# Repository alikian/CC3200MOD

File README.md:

CC3200MOD Eagle Library and Breakout
=======================

Eagle Library for TI CC3200MOD and CC3200MOD Breakout board

For more info about Breakout please check the WiKi page https://github.com/alikian/CC3200MOD/wiki

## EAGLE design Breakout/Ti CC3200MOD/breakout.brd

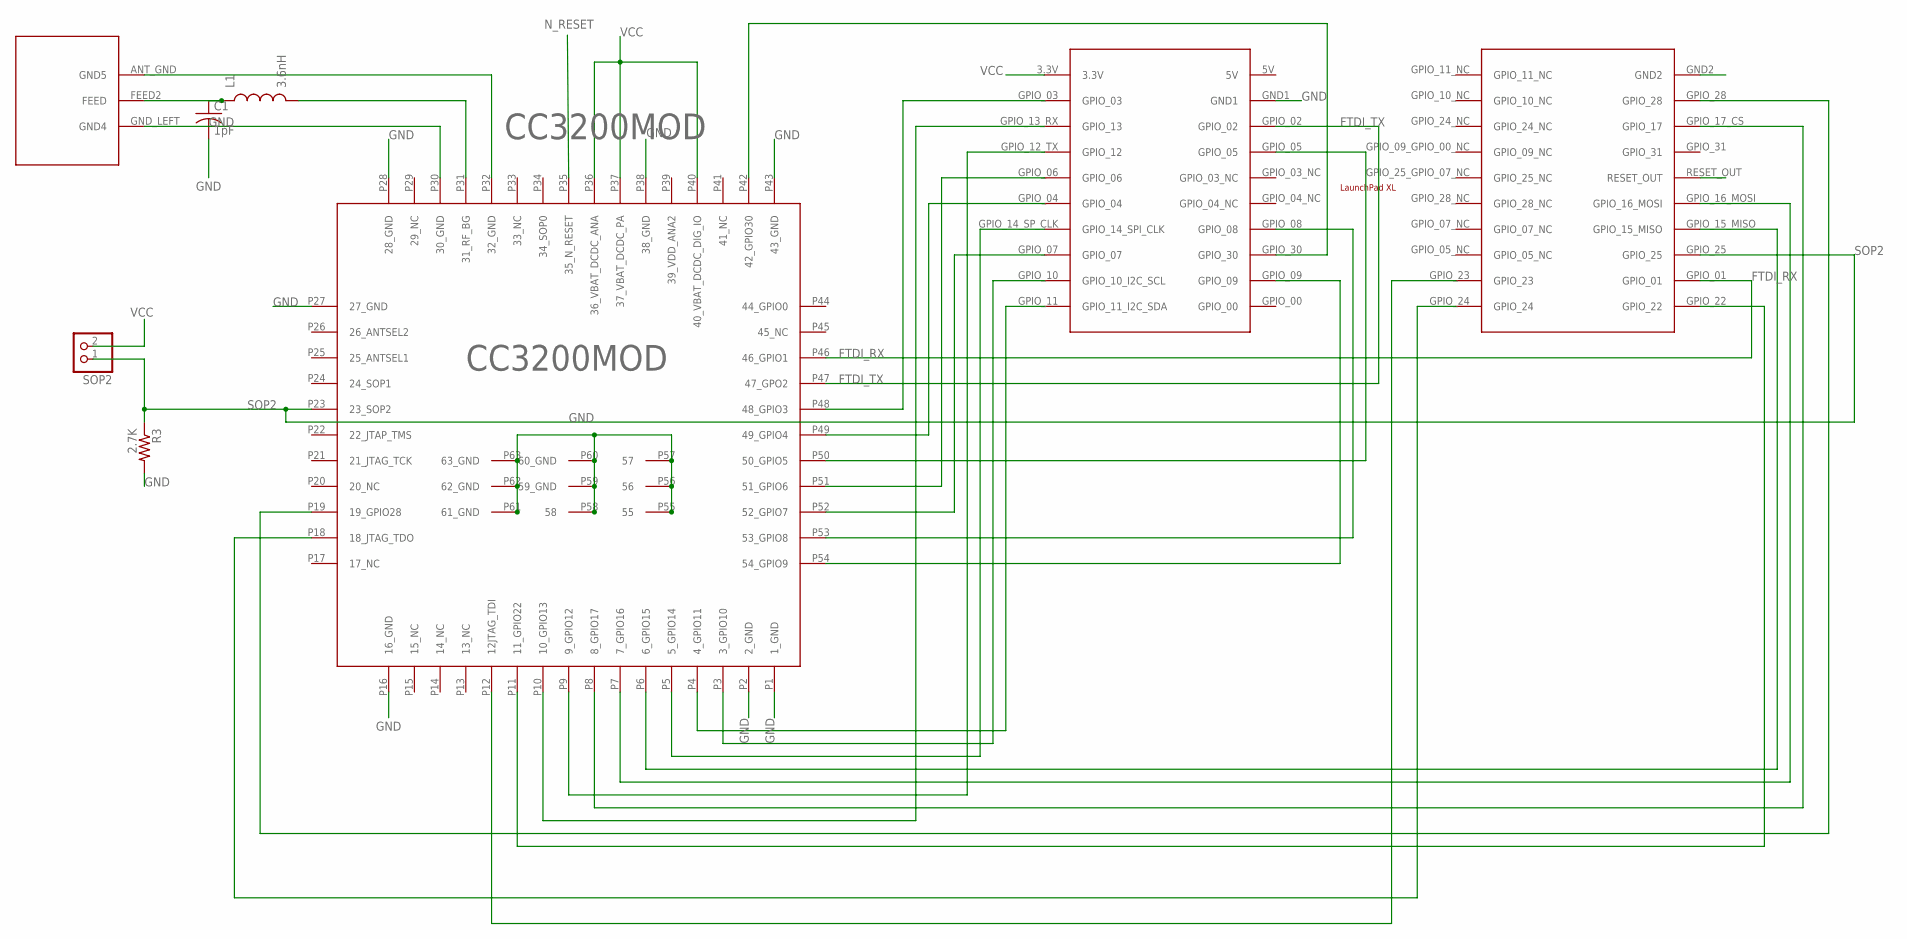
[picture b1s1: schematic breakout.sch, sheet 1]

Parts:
ANT_PAD: ANT
C1: 1pF; C0402
CC3200MOD: CC3200; CC3200MOD
L1: 3.6nH; C0402
R3: 2.7K; 0603-RES
SOP2: PINHD-1X2; 1X02
U11: XL; LAUNCHPADXL

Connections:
FTDI_RX: CC3200MOD.P46 (46_GPIO1), U11.GPIO_01; also elsewhere on the board
FTDI_TX: CC3200MOD.P47 (47_GPO2), U11.GPIO_02; also elsewhere on the board
GND: ANT_PAD.ANT_GND (GND5), ANT_PAD.GND_LEFT (GND4), C1.2, CC3200MOD.P1 (1_GND), CC3200MOD.P2 (2_GND), CC3200MOD.P16 (16_GND), CC3200MOD.P27 (27_GND), CC3200MOD.P28 (28_GND), CC3200MOD.P30 (30_GND), CC3200MOD.P32 (32_GND), CC3200MOD.P38 (38_GND), CC3200MOD.P43 (43_GND), CC3200MOD.P55 (55), CC3200MOD.P56 (56), CC3200MOD.P57 (57), CC3200MOD.P58 (58), CC3200MOD.P59 (59_GND), CC3200MOD.P60 (60_GND), CC3200MOD.P61 (61_GND), CC3200MOD.P62 (62_GND), CC3200MOD.P63 (63_GND), R3.2, U11.GND1, U11.GND2; also elsewhere on the board
GPIO_05: CC3200MOD.P50 (50_GPIO5), U11.GPIO_05; also elsewhere on the board
GPIO_10: CC3200MOD.P3 (3_GPIO10), U11.GPIO_10 (GPIO_10_I2C_SCL); also elsewhere on the board
GPIO_11: CC3200MOD.P4 (4_GPIO11), U11.GPIO_11 (GPIO_11_I2C_SDA); also elsewhere on the board
GPIO_13: CC3200MOD.P10 (10_GPIO13), U11.GPIO_13_RX (GPIO_13); also elsewhere on the board
GPIO_22: CC3200MOD.P11 (11_GPIO22), U11.GPIO_22
GPIO_30: CC3200MOD.P42 (42_GPIO30), U11.GPIO_30; also elsewhere on the board
JTAG_TDI: CC3200MOD.P12 (12JTAG_TDI), U11.GPIO_23
JTAG_TDO: CC3200MOD.P18 (18_JTAG_TDO), U11.GPIO_24
unnamed: ANT_PAD.FEED2 (FEED), C1.1, L1.1
unnamed: CC3200MOD.P31 (31_RF_BG), L1.2
unnamed: CC3200MOD.P6 (6_GPIO15), U11.GPIO_15_MISO
unnamed: CC3200MOD.P7 (7_GPIO16), U11.GPIO_16_MOSI
unnamed: CC3200MOD.P8 (8_GPIO17), U11.GPIO_17_CS (GPIO_17)
unnamed: CC3200MOD.P5 (5_GPIO14), U11.GPIO_14_SP_CLK (GPIO_14_SPI_CLK)
unnamed: CC3200MOD.P19 (19_GPIO28), U11.GPIO_28
unnamed: CC3200MOD.P51 (51_GPIO6), U11.GPIO_06
unnamed: CC3200MOD.P49 (49_GPIO4), U11.GPIO_04
unnamed: CC3200MOD.P52 (52_GPIO7), U11.GPIO_07
unnamed: CC3200MOD.P53 (53_GPIO8), U11.GPIO_08
unnamed: CC3200MOD.P54 (54_GPIO9), U11.GPIO_09
unnamed: CC3200MOD.P9 (9_GPIO12), U11.GPIO_12_TX (GPIO_12)
unnamed: CC3200MOD.P48 (48_GPIO3), U11.GPIO_03
N_RESET: CC3200MOD.P35 (35_N_RESET), U11.RESET_OUT; also elsewhere on the board
SOP2: CC3200MOD.P23 (23_SOP2), R3.1, SOP2.1, U11.GPIO_25; also elsewhere on the board
VCC: CC3200MOD.P36 (36_VBAT_DCDC_ANA), CC3200MOD.P37 (37_VBAT_DCDC_PA), CC3200MOD.P40 (40_VBAT_DCDC_DIG_IO), SOP2.2, U11.3.3V; also elsewhere on the board

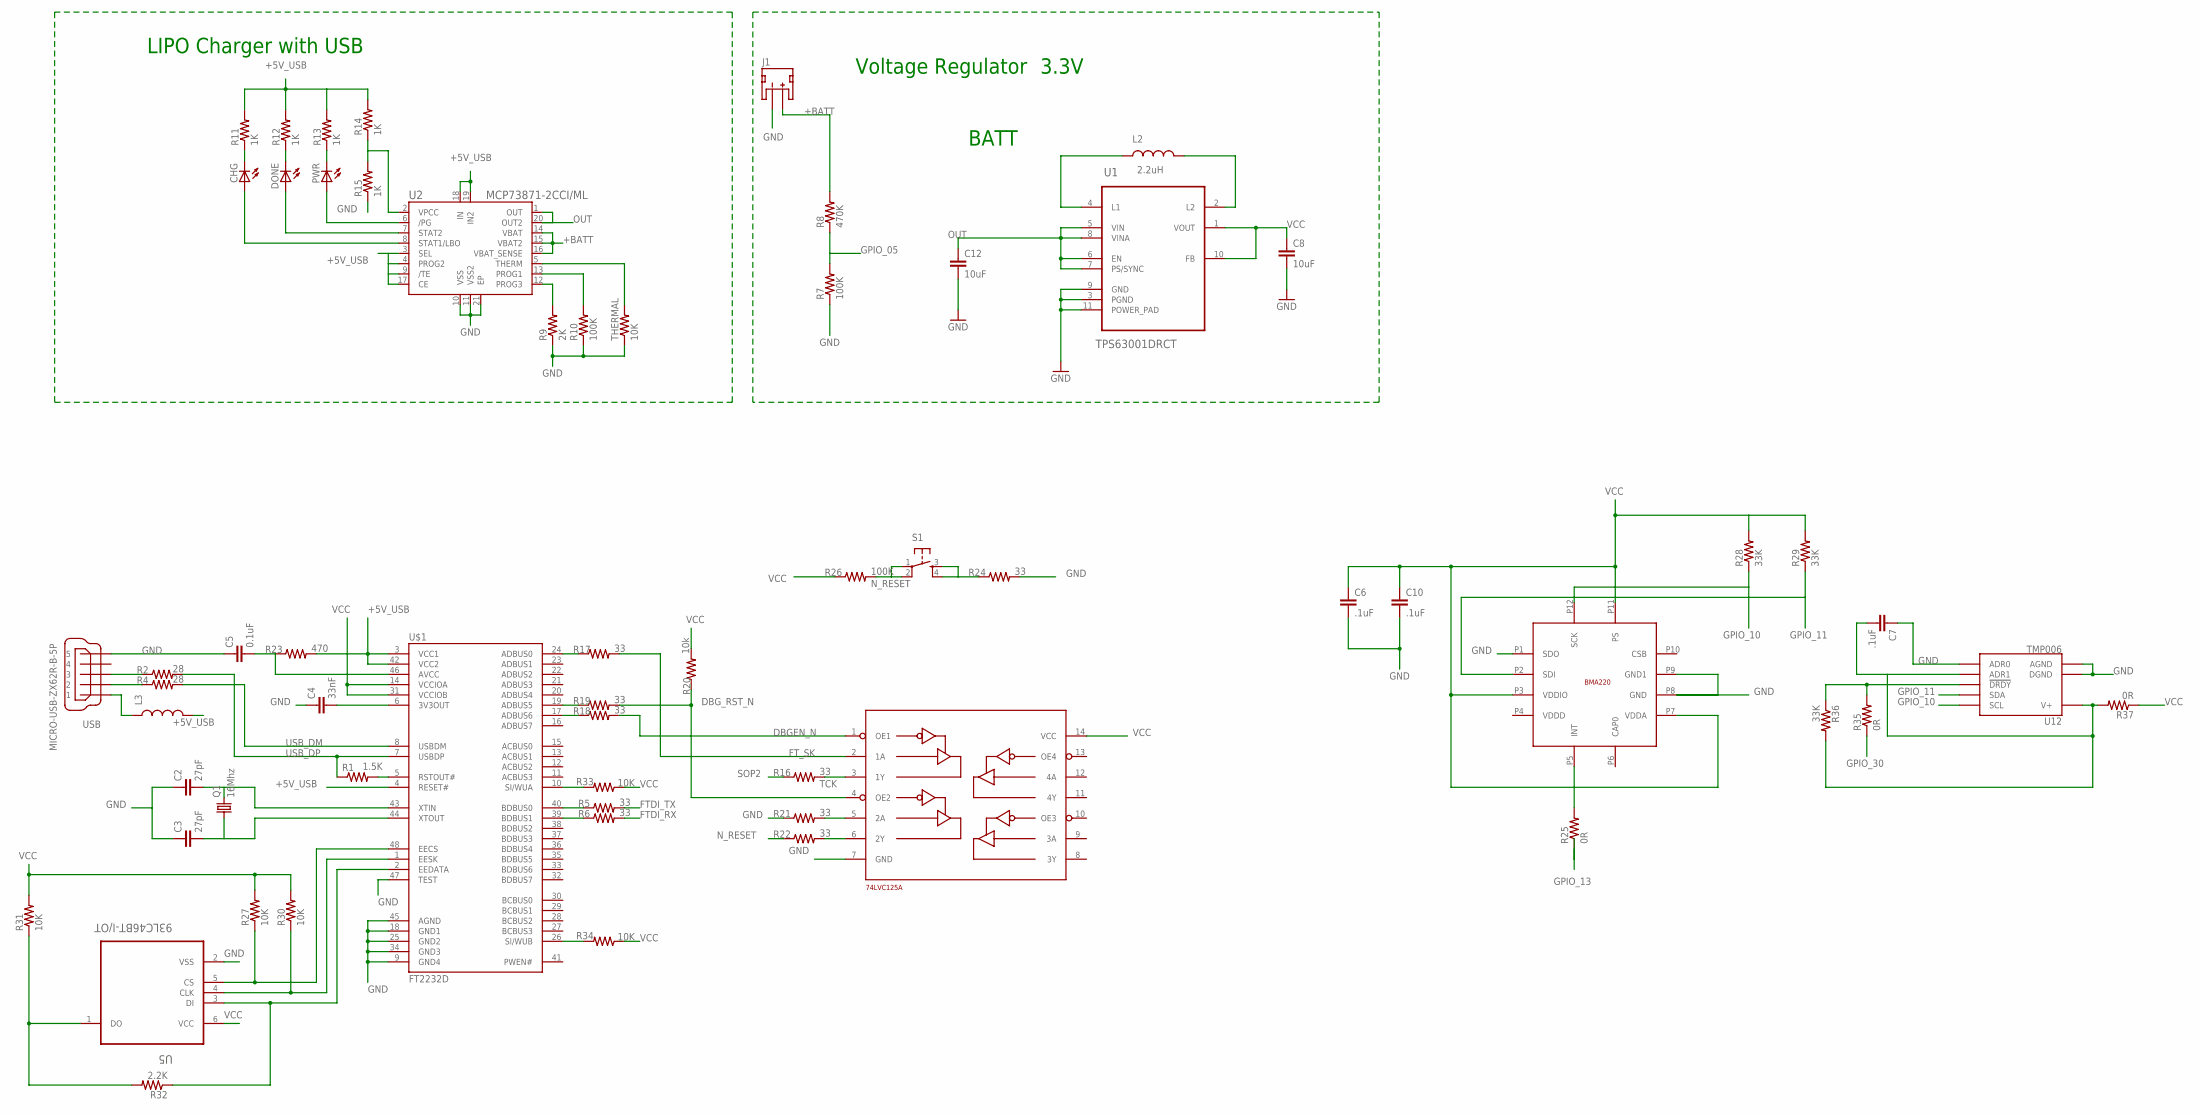
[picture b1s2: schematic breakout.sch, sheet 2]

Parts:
C2, C3: 27pF; 0402-CAP
C4: 33nF; 0402-CAP
C5: 0.1uF; 0402-CAP
C6, C7, C10: .1uF; 0402-CAP
C8, C12: 10uF; C0603
CHG: LEDSML0603; SML0603
DONE: LEDSML0603; SML0603
J1: JST_2MM_MALE; JST-2-SMD
L2: 2.2uH; 0805
L3: INDUCTOR-SPARKFUN0603; 0603
PWR: LEDSML0603; SML0603
Q1: 16Mhz; TC26H
R1: 1.5K; 0603-RES
R2, R4: 28; 0603-RES
R5, R6, R16, R17, R18, R19, R21, R22, R24: 33; 0603-RES
R7, R10, R26: 100K; 0603-RES
R8: 470K; 0603-RES
R9: 2K; 0603-RES
R11, R12, R13, R14, R15: 1K; 0603-RES
R20: 10k; 0603-RES
R23: 470; 0603-RES
R25, R35, R37: 0R; 0603-RES
R27, R30, R31, R33, R34: 10K; 0402-RES
R28, R29, R36: 33K; 0402-RES
R32: 2.2K; 0402-RES
S1: TAC_SWITCHSMD; TACTILE_SWITCH_SMD
THERMAL: 10K; 0603-RES
U1: TPS63001DRCT; SON50P300X300X100-11N
U2: MCP73871-2CCI/ML; QFN20-4X4
U5: 93LC46BT-I/OT; SOT95P280X145-6N
U12: TMP006; BGA8DS
U$1: FT2232D; LQFP-48
U$3: DECADE-74LVC125A; DECADE-SO-14
U$4: BMA220; BMA222
USB: MICRO-USB-ZX62R-B-5P; ZX62R-B-5P

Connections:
+5V_USB: L3.2, R11.2, R12.2, R13.2, R14.2, R23.2, U2.3 (SEL), U2.4 (PROG2), U2.9 (/TE), U2.17 (CE), U2.18 (IN), U2.19 (IN2), U$1.3 (VCC1), U$1.4 (RESET#), U$1.42 (VCC2)
+BATT: J1.2 (+), R8.2, U2.14 (VBAT), U2.15 (VBAT2), U2.16 (VBAT_SENSE)
DBGEN_N: R18.2, U$3.1 (OE1)
DBG_RST_N: R19.2, R20.1, U$3.4 (OE2)
FTDI_RX: R6.2; also elsewhere on the board
FTDI_TX: R5.2; also elsewhere on the board
FT_SK: R17.2, U$3.2 (1A)
GND: C2.1, C3.1, C4.1, C5.1, C6.2, C7.1, C8.2, C10.2, C12.2, J1.1 (-), R7.1, R9.1, R10.1, R15.1, R21.1, R24.2, THERMAL.1, U1.3 (PGND), U1.9 (GND), U1.11 (POWER_PAD), U2.10 (VSS), U2.11 (VSS2), U2.21 (EP), U5.2 (VSS), U12.A1 (DGND), U12.A2 (AGND), U12.C1 (ADR0), U$1.9 (GND4), U$1.18 (GND1), U$1.25 (GND2), U$1.34 (GND3), U$1.45 (AGND), U$1.47 (TEST), U$3.7 (GND), U$4.P1 (SDO), U$4.P8 (GND), U$4.P9 (GND1), USB.5; also elsewhere on the board
GPIO_05: R7.2, R8.1; also elsewhere on the board
GPIO_10: R28.1, U12.B3 (SCL), U$4.P12 (SCK); also elsewhere on the board
GPIO_11: R29.1, U12.C3 (SDA), U$4.P2 (SDI); also elsewhere on the board
GPIO_13: R25.1; also elsewhere on the board
GPIO_30: R35.1; also elsewhere on the board
unnamed: R1.2, U$1.5 (RSTOUT#)
unnamed: C7.2, R36.2, R37.2, U12.A3 (V+), U12.B1 (ADR1)
unnamed: L3.1, USB.1
unnamed: R4.1, USB.2
unnamed: R9.2, U2.12 (PROG3)
unnamed: R10.2, U2.13 (PROG1)
unnamed: R2.1, USB.3
unnamed: PWR.A, U2.6 (/PG)
unnamed: THERMAL.2, U2.5 (THERM)
unnamed: L2.1, U1.4 (L1)
unnamed: L2.2, U1.2 (L2)
unnamed: DONE.A, U2.7 (STAT2)
unnamed: CHG.A, U2.8 (STAT1/LBO)
unnamed: CHG.C, R11.1
unnamed: DONE.C, R12.1
unnamed: PWR.C, R13.1
unnamed: R14.1, R15.2, U2.2 (VPCC)
unnamed: C2.2, Q1.2, U$1.43 (XTIN)
unnamed: R27.1, U5.5 (CS), U$1.48 (EECS)
unnamed: C3.2, Q1.1, U$1.44 (XTOUT)
unnamed: R30.1, U5.4 (CLK), U$1.1 (EESK)
unnamed: R32.1, U5.3 (DI), U$1.2 (EEDATA)
unnamed: C4.2, U$1.6 (3V3OUT)
unnamed: R5.1, U$1.40 (BDBUS0)
unnamed: R6.1, U$1.39 (BDBUS1)
unnamed: R17.1, U$1.24 (ADBUS0)
unnamed: R19.1, U$1.19 (ADBUS5)
unnamed: R18.1, U$1.17 (ADBUS6)
unnamed: R21.2, U$3.5 (2A)
unnamed: R22.2, U$3.6 (2Y)
unnamed: C5.2, R23.1, U$1.46 (AVCC)
unnamed: R25.2, U$4.P5 (INT)
unnamed: R24.1, S1.3, S1.4
unnamed: R31.1, R32.2, U5.1 (DO)
unnamed: R33.2, U$1.10 (SI/WUA)
unnamed: R34.2, U$1.26 (SI/WUB)
unnamed: R35.2, R36.1, U12.C2 (!DRDY)
N_RESET: R22.1, R26.2, S1.1, S1.2; also elsewhere on the board
OUT: C12.1, U1.5 (VIN), U1.6 (EN), U1.7 (PS/SYNC), U1.8 (VINA), U2.1 (OUT), U2.20 (OUT2)
SOP2: R16.1; also elsewhere on the board
TCK: R16.2, U$3.3 (1Y)
USB_DM: R4.2, U$1.8 (USBDM)
USB_DP: R1.1, R2.2, U$1.7 (USBDP)
VCC: C6.1, C8.1, C10.1, R20.2, R26.1, R27.2, R28.2, R29.2, R30.2, R31.2, R33.1, R37.1, U1.1 (VOUT), U1.10 (FB), U5.6 (VCC), U$1.14 (VCCIOA), U$1.31 (VCCIOB), U$3.14 (VCC), U$4.P3 (VDDIO), U$4.P7 (VDDA), U$4.P11 (PS); also elsewhere on the board

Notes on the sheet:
BATT
LIPO Charger with USB
Voltage Regulator
3.3V

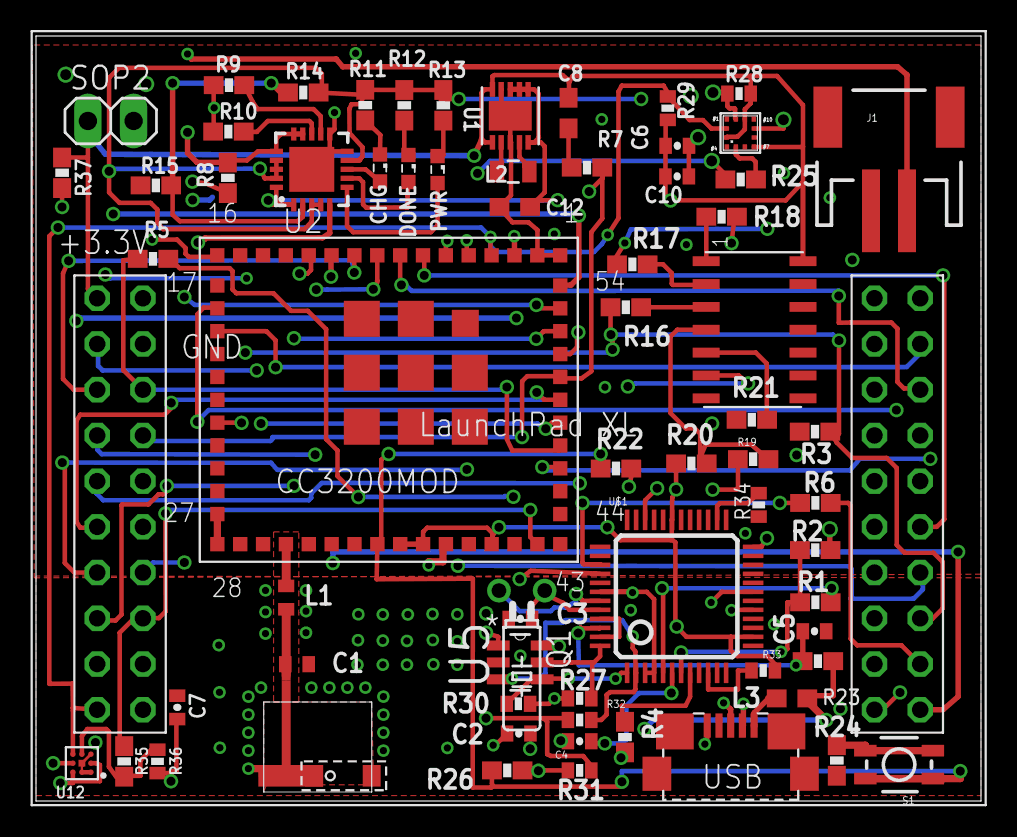
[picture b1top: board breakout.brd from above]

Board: 4 copper layers, 52.5 x 42.5 mm, 69 parts (1 on the bottom side), 74 nets.

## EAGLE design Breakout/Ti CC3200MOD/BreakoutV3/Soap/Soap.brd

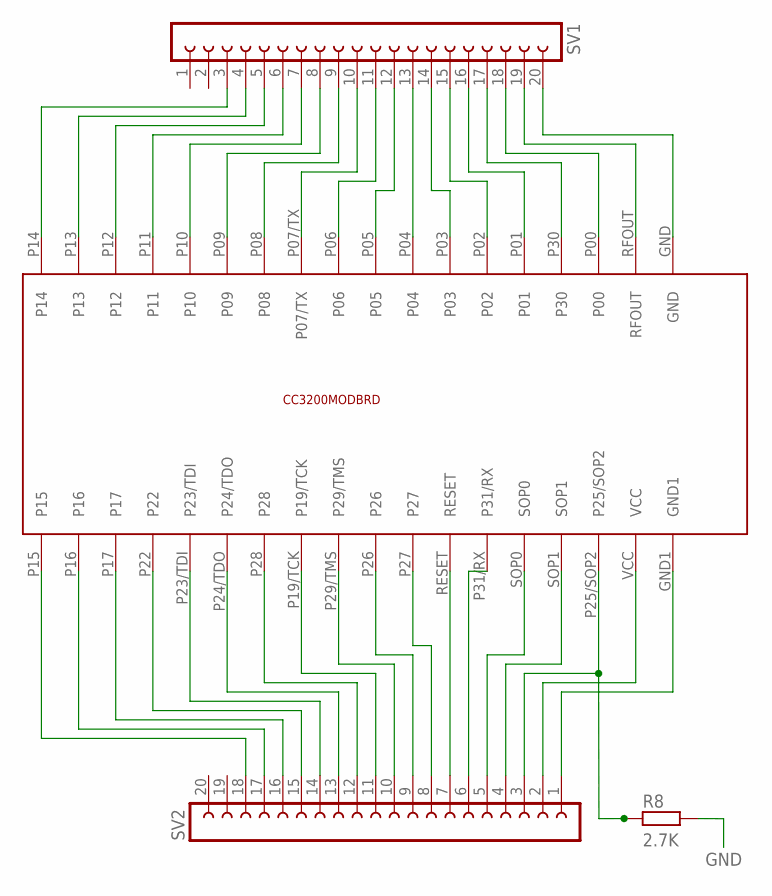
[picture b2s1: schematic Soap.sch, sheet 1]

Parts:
R8: 2.7K; R0603
SV1, SV2: FE20-1; FE20
U$1: CC3200MOD

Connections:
+3V3: SV2.2, U$1.VCC
GND: R8.2, SV1.20, SV2.1, U$1.GND, U$1.GND1; also elsewhere on the board
unnamed: SV2.18, U$1.P15
unnamed: SV2.17, U$1.P16
unnamed: SV2.16, U$1.P17
unnamed: SV2.15, U$1.P22
unnamed: SV2.14, U$1.P23/TDI
unnamed: SV2.13, U$1.P24/TDO
unnamed: SV2.12, U$1.P28
unnamed: SV2.11, U$1.P19/TCK
unnamed: SV1.3, U$1.P14
unnamed: SV1.4, U$1.P13
unnamed: SV1.5, U$1.P12
unnamed: SV1.6, U$1.P11
unnamed: SV1.7, U$1.P10
unnamed: SV1.8, U$1.P09
unnamed: SV1.9, U$1.P08
unnamed: SV1.10, U$1.P07/TX
unnamed: SV1.11, U$1.P06
unnamed: SV1.12, U$1.P05
unnamed: SV1.13, U$1.P04
unnamed: SV1.14, U$1.P03
unnamed: SV1.15, U$1.P02
unnamed: SV1.16, U$1.P01
unnamed: SV1.17, U$1.P30
unnamed: SV1.18, U$1.P00
unnamed: SV1.19, U$1.RFOUT
unnamed: SV2.9, U$1.P26
unnamed: SV2.8, U$1.P27
unnamed: SV2.7, U$1.RESET
unnamed: SV2.6, U$1.P31/RX
unnamed: SV2.5, U$1.SOP0
unnamed: SV2.4, U$1.SOP1
SOP2: R8.1, SV2.3, U$1.P25/SOP2

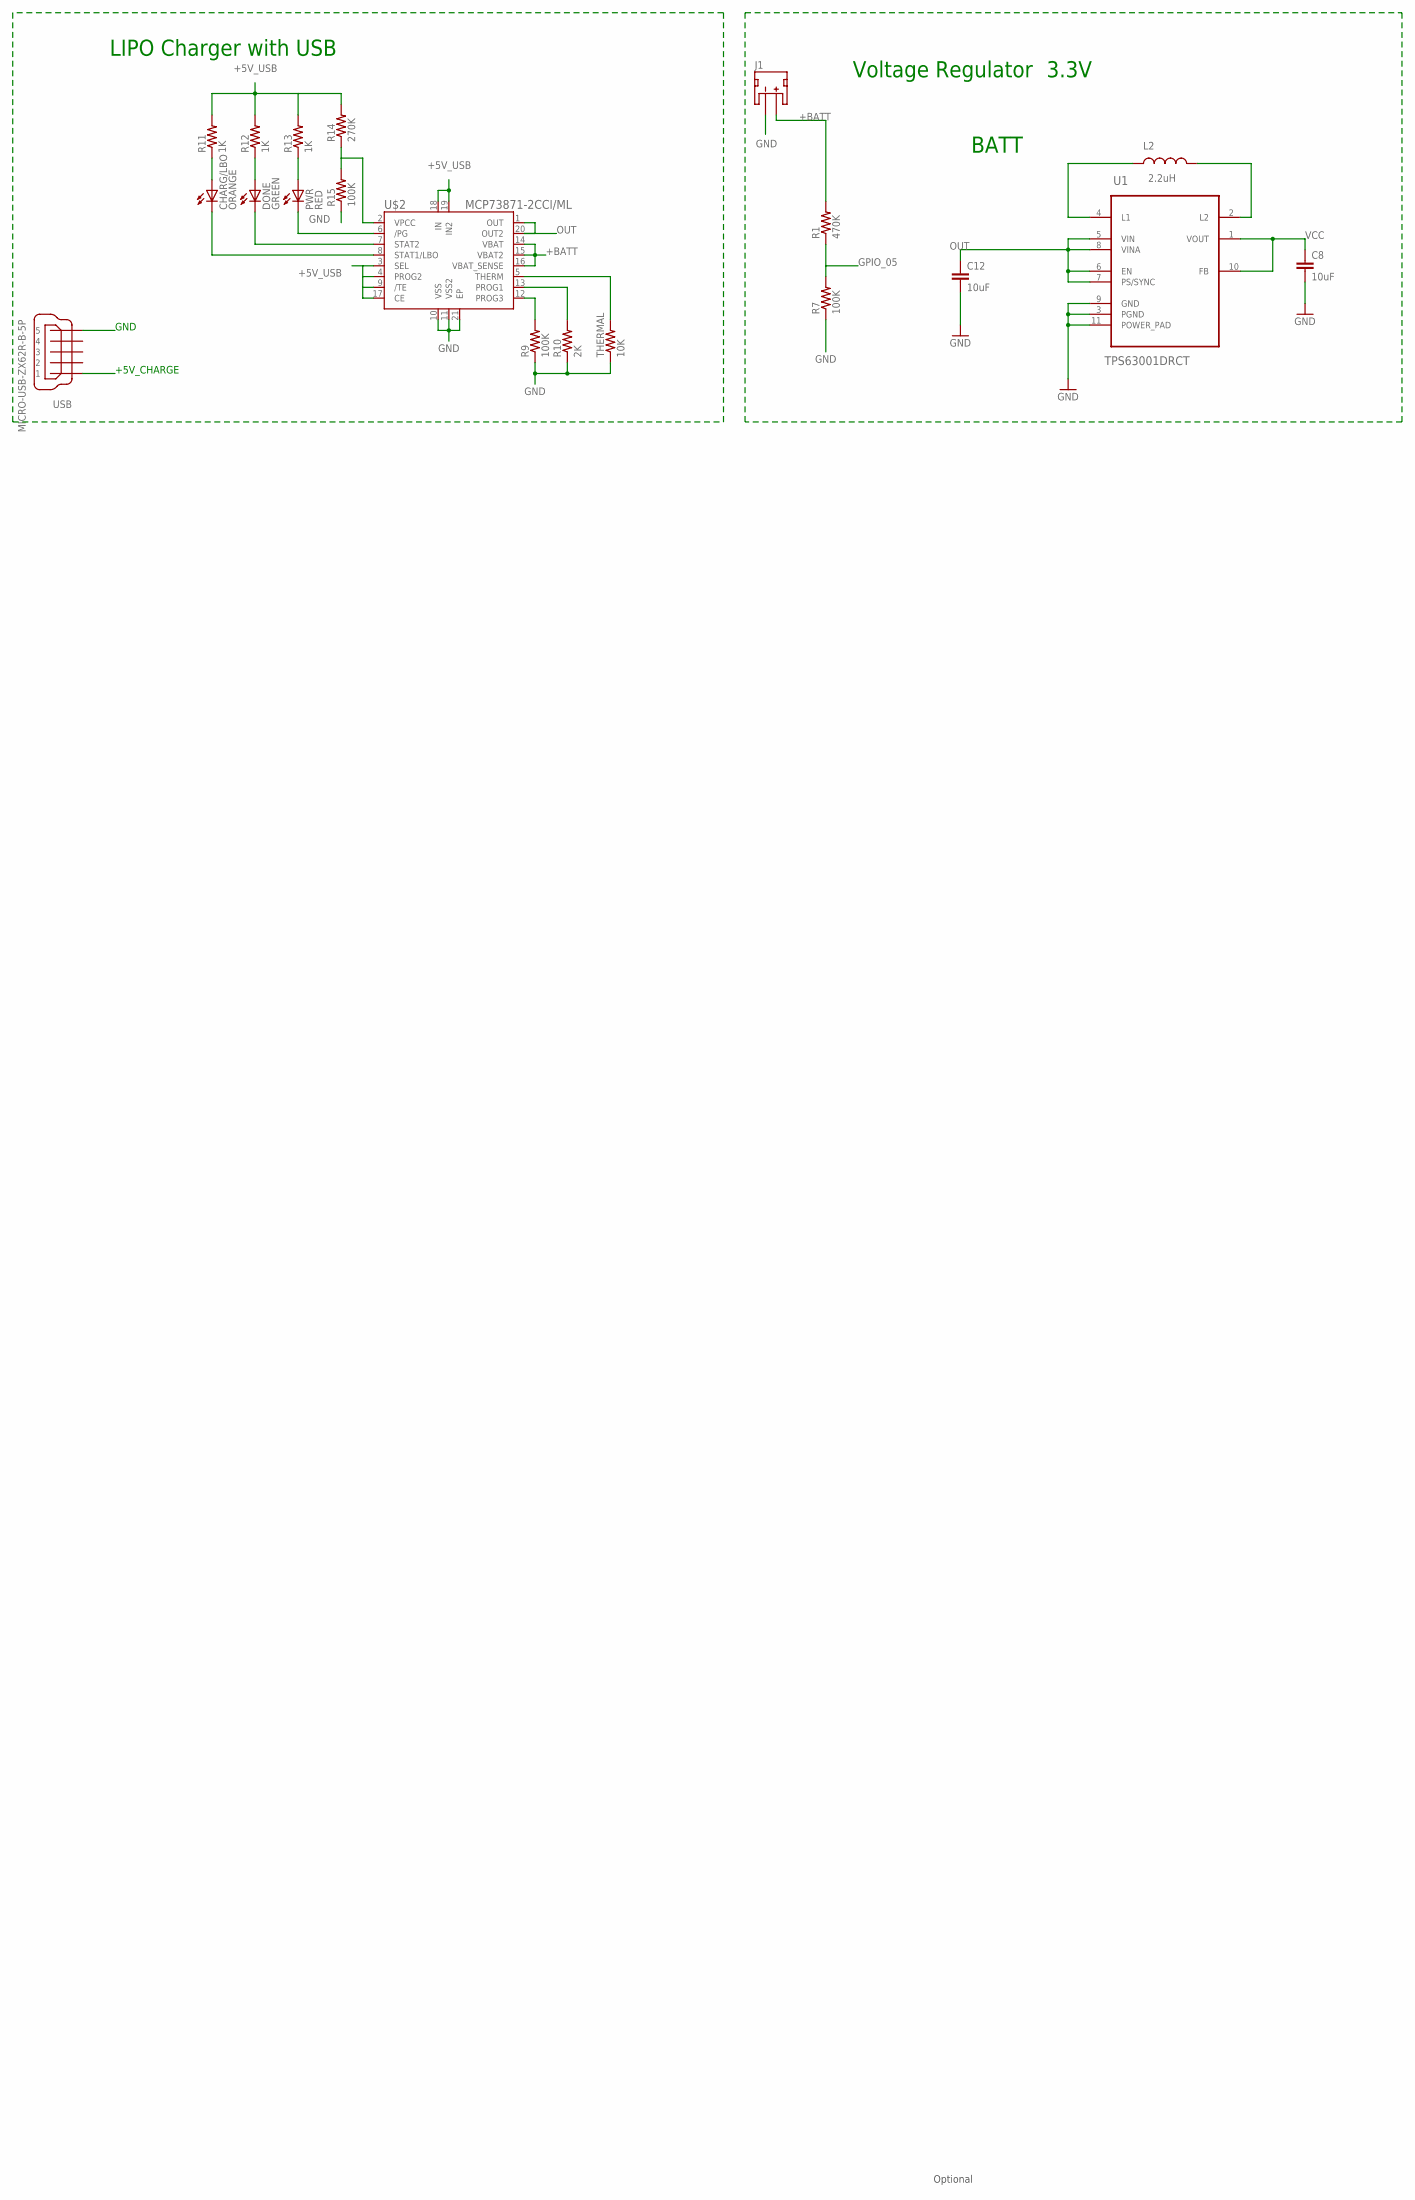
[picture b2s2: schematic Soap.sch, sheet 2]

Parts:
C8, C12: 10uF; C0603
CHARG/LBO: ORANGE; SML0603
DONE: GREEN; SML0603
J1: JST_2MM_MALE; JST-2-SMD
L2: 2.2uH; 0805
PWR: RED; SML0603
R1: 470K; 0603-RES
R7, R9, R15: 100K; 0603-RES
R10: 2K; 0603-RES
R11, R12, R13: 1K; 0603-RES
R14: 270K; 0603-RES
THERMAL: 10K; 0603-RES
U1: TPS63001DRCT; SON50P300X300X100-11N
U$2: MCP73871-2CCI/ML; QFN20-4X4
USB: MICRO-USB-ZX62R-B-5P; ZX62R-B-5P

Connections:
+5V_USB: R11.2, R12.2, R13.2, R14.2, U$2.3 (SEL), U$2.4 (PROG2), U$2.9 (/TE), U$2.17 (CE), U$2.18 (IN), U$2.19 (IN2), USB.1
+BATT: J1.2 (+), R1.2, U$2.14 (VBAT), U$2.15 (VBAT2), U$2.16 (VBAT_SENSE)
GND: C8.2, C12.2, J1.1 (-), R7.1, R9.1, R10.1, R15.1, THERMAL.1, U1.3 (PGND), U1.9 (GND), U1.11 (POWER_PAD), U$2.10 (VSS), U$2.11 (VSS2), U$2.21 (EP), USB.5; also elsewhere on the board
GPIO_05: R1.1, R7.2
unnamed: CHARG/LBO.A, R11.1
unnamed: DONE.A, R12.1
unnamed: PWR.A, R13.1
unnamed: L2.1, U1.4 (L1)
unnamed: L2.2, U1.2 (L2)
unnamed: R9.2, U$2.12 (PROG3)
unnamed: R10.2, U$2.13 (PROG1)
unnamed: PWR.C, U$2.6 (/PG)
unnamed: DONE.C, U$2.7 (STAT2)
unnamed: CHARG/LBO.C, U$2.8 (STAT1/LBO)
unnamed: R14.1, R15.2, U$2.2 (VPCC)
unnamed: THERMAL.2, U$2.5 (THERM)
OUT: C12.1, U1.5 (VIN), U1.6 (EN), U1.7 (PS/SYNC), U1.8 (VINA), U$2.1 (OUT), U$2.20 (OUT2)
VCC: C8.1, U1.1 (VOUT), U1.10 (FB)

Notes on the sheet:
Optional
BATT
LIPO Charger with USB
Voltage Regulator
3.3V
+5V_CHARGE
GND

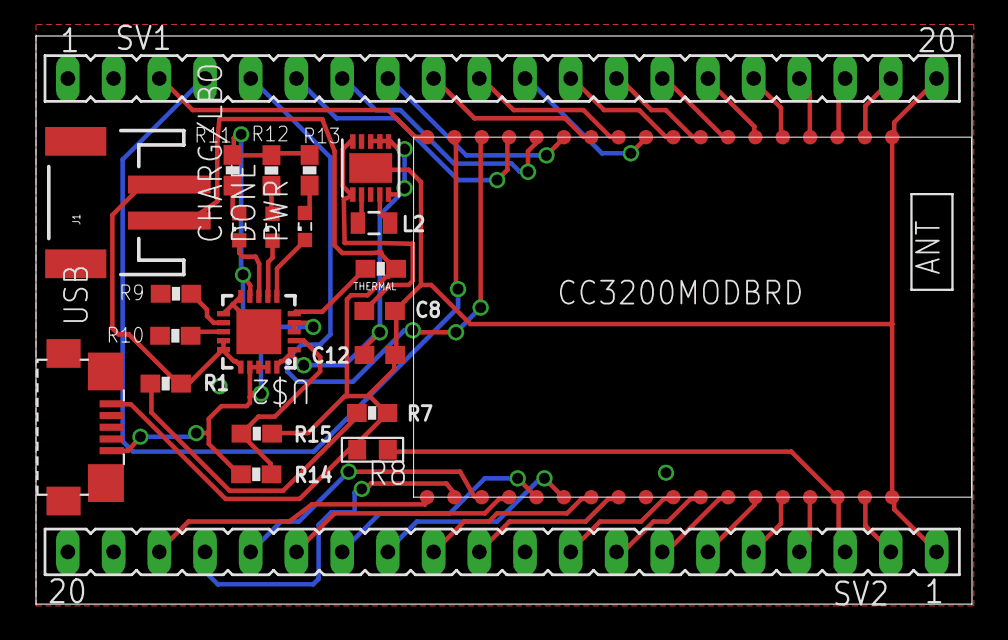
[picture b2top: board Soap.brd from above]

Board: 2 copper layers, 52.0 x 31.6 mm, 24 parts (0 on the bottom side), 51 nets.

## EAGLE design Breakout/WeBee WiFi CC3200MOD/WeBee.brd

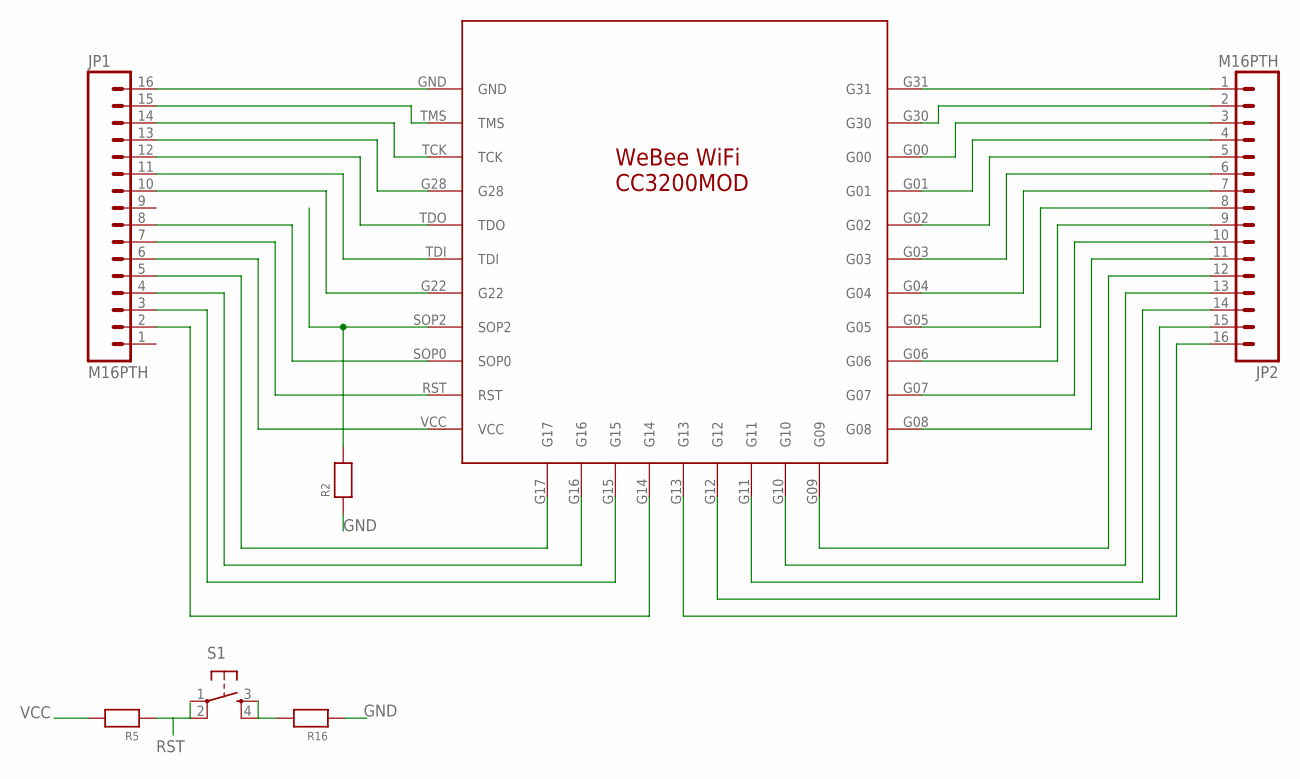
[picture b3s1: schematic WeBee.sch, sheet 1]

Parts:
JP1, JP2: M16PTH; 1X16
R2, R5, R16: RESISTOR0402; 0402
S1: TAC_SWITCHSMD; TACTILE_SWITCH_SMD
U$1: WEBEE_WIFI_CC3200; CC3200

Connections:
FTDI_RX: JP2.4, U$1.G01; also elsewhere on the board
FTDI_TX: JP2.5, U$1.G02; also elsewhere on the board
G00: JP2.3, U$1.G00
GND: JP1.16, R2.1, R16.1, U$1.GND; also elsewhere on the board
unnamed: R16.2, S1.3, S1.4
unnamed: JP1.15, U$1.TMS
unnamed: JP1.14, U$1.TCK
unnamed: JP1.13, U$1.G28
unnamed: JP1.12, U$1.TDO
unnamed: JP1.11, U$1.TDI
unnamed: JP1.10, U$1.G22
unnamed: JP1.8, U$1.SOP0
unnamed: JP2.1, U$1.G31
unnamed: JP2.2, U$1.G30
unnamed: JP2.6, U$1.G03
unnamed: JP2.7, U$1.G04
unnamed: JP2.8, U$1.G05
unnamed: JP2.9, U$1.G06
unnamed: JP2.10, U$1.G07
unnamed: JP2.11, U$1.G08
unnamed: JP2.12, U$1.G09
unnamed: JP1.5, U$1.G17
unnamed: JP2.13, U$1.G10
unnamed: JP2.14, U$1.G11
unnamed: JP2.15, U$1.G12
unnamed: JP2.16, U$1.G13
unnamed: JP1.4, U$1.G16
unnamed: JP1.3, U$1.G15
unnamed: JP1.2, U$1.G14
RST: JP1.7, R5.1, S1.2, U$1.RST; also elsewhere on the board
SOP2: R2.2, U$1.SOP2; also elsewhere on the board
VCC: JP1.6, R5.2, U$1.VCC; also elsewhere on the board

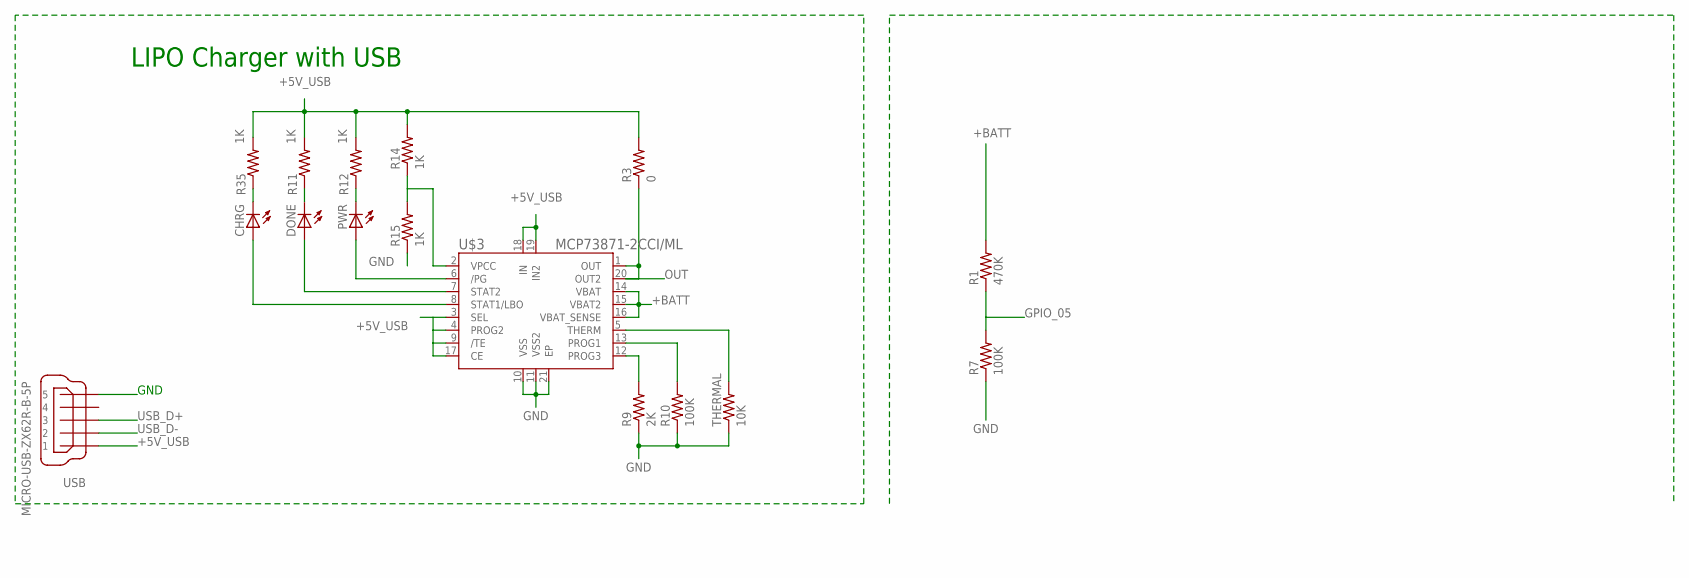
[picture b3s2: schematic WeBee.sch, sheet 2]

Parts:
CHRG: LEDSML0603; SML0603
DONE: LEDSML0603; SML0603
PWR: LEDSML0603; SML0603
R1: 470K; 0603-RES
R3: 0; 0603-RES
R7, R10: 100K; 0603-RES
R9: 2K; 0603-RES
R11, R12, R35: 1K; 0402-RES
R14, R15: 1K; 0603-RES
THERMAL: 10K; 0603-RES
U$3: MCP73871-2CCI/ML; QFN20-4X4
USB: MICRO-USB-ZX62R-B-5P; ZX62R-B-5P

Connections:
+5V_USB: R3.2, R11.2, R12.2, R14.2, R35.2, U$3.3 (SEL), U$3.4 (PROG2), U$3.9 (/TE), U$3.17 (CE), U$3.18 (IN), U$3.19 (IN2), USB.1; also elsewhere on the board
+BATT: R1.2, U$3.14 (VBAT), U$3.15 (VBAT2), U$3.16 (VBAT_SENSE); also elsewhere on the board
GND: R7.1, R9.1, R10.1, R15.1, THERMAL.1, U$3.10 (VSS), U$3.11 (VSS2), U$3.21 (EP), USB.5; also elsewhere on the board
GPIO_05: R1.1, R7.2
unnamed: R9.2, U$3.12 (PROG3)
unnamed: R10.2, U$3.13 (PROG1)
unnamed: PWR.A, U$3.6 (/PG)
unnamed: DONE.A, U$3.7 (STAT2)
unnamed: CHRG.A, U$3.8 (STAT1/LBO)
unnamed: CHRG.C, R35.1
unnamed: DONE.C, R11.1
unnamed: PWR.C, R12.1
unnamed: R14.1, R15.2, U$3.2 (VPCC)
unnamed: THERMAL.2, U$3.5 (THERM)
OUT: R3.1, U$3.1 (OUT), U$3.20 (OUT2); also elsewhere on the board
USB_D+: USB.3; also elsewhere on the board
USB_D-: USB.2; also elsewhere on the board

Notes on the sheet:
LIPO Charger with USB
GND

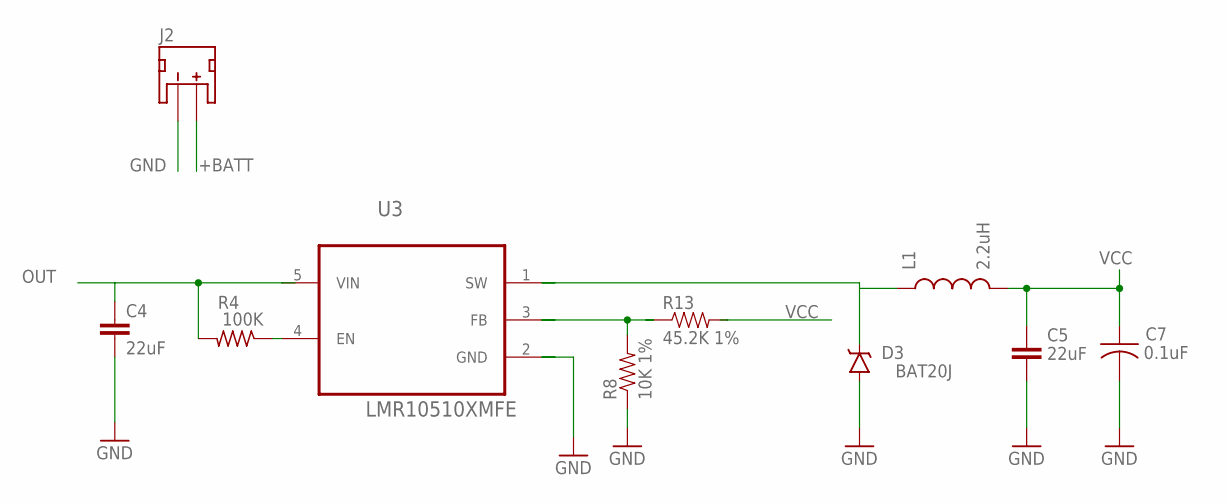
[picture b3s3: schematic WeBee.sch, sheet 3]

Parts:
C4, C5: 22uF; C0603
C7: 0.1uF; C0402
D3: BAT20J; SOD-323
J2: JST_2MM_MALE; JST-2-SMD
L1: 2.2uH; 0805
R4: 100K; R0402
R8: 10K 1%; 0402-RES
R13: 45.2K 1%; 0402-RES
U3: LMR10510XMFE; SOT95P270X145-5N

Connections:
+BATT: J2.2 (+); also elsewhere on the board
FB: R8.2, R13.1, U3.3 (FB)
GND: C4.2, C5.2, C7.2, D3.A, J2.1 (-), R8.1, U3.2 (GND); also elsewhere on the board
unnamed: R4.1, U3.4 (EN)
OUT: C4.1, R4.2, U3.5 (VIN); also elsewhere on the board
SW: D3.C, L1.1, U3.1 (SW)
VCC: C5.1, C7.1, L1.2, R13.2; also elsewhere on the board

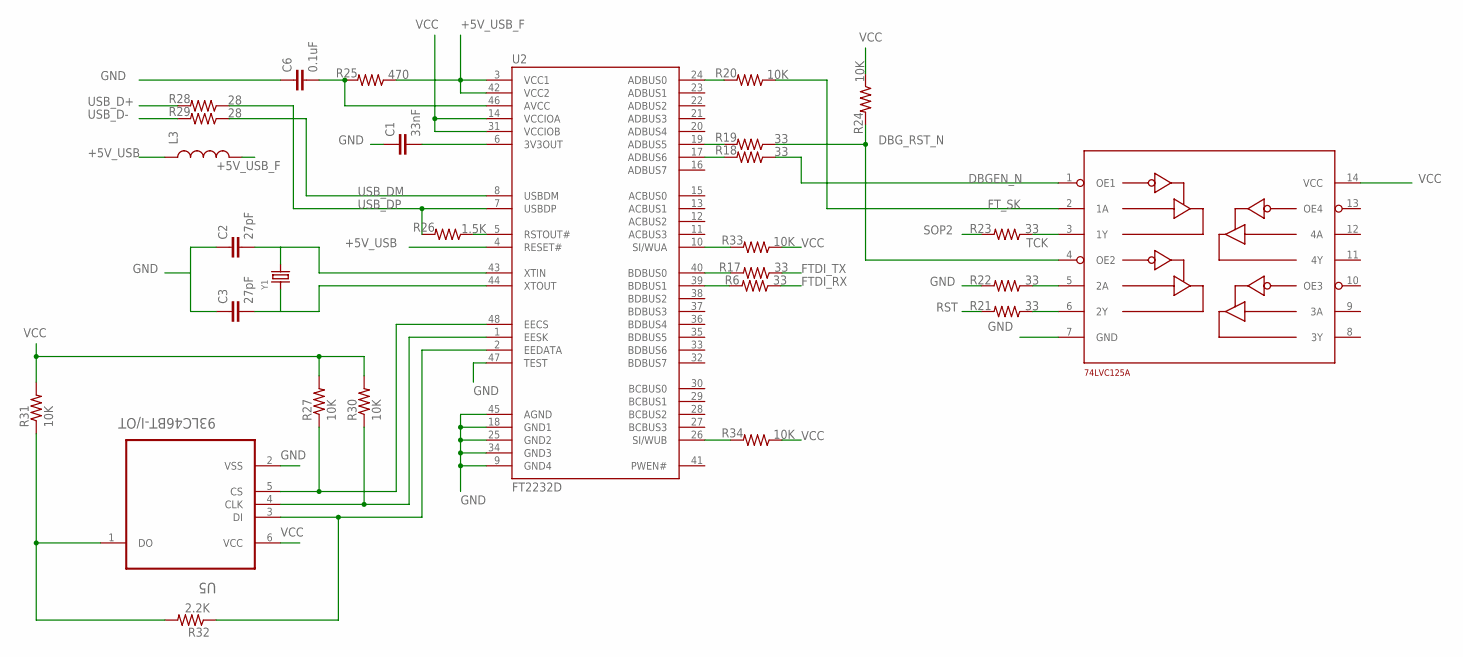
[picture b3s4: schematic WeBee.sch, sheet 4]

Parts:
C1: 33nF; 0402-CAP
C2, C3: 27pF; 0402-CAP
C6: 0.1uF; 0402-CAP
L3: INDUCTOR-SPARKFUN0603; 0603
R6, R17, R18, R19, R21, R22, R23: 33; 0402-RES
R20, R24, R27, R30, R31, R33, R34: 10K; 0402-RES
R25: 470; 0402-RES
R26: 1.5K; 0402-RES
R28, R29: 28; 0402-RES
R32: 2.2K; 0402-RES
U2: FT2232D; LQFP-48
U5: 93LC46BT-I/OT; SOT95P280X145-6N
U$4: DECADE-74LVC125A; DECADE-SO-14
Y1: CRYSTAL2.5X2.0MM; CRYSTAL_2.5X2

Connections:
+5V_USB: L3.1, U2.4 (RESET#); also elsewhere on the board
+5V_USB_F: L3.2, R25.1, U2.3 (VCC1), U2.42 (VCC2)
DBGEN_N: R18.1, U$4.1 (OE1)
DBG_RST_N: R19.1, R24.2, U$4.4 (OE2)
FTDI_RX: R6.1; also elsewhere on the board
FTDI_TX: R17.1; also elsewhere on the board
FT_SK: R20.1, U$4.2 (1A)
GND: C1.1, C2.1, C3.1, C6.1, R22.2, U2.9 (GND4), U2.18 (GND1), U2.25 (GND2), U2.34 (GND3), U2.45 (AGND), U2.47 (TEST), U5.2 (VSS), U$4.7 (GND); also elsewhere on the board
unnamed: R26.1, U2.5 (RSTOUT#)
unnamed: C2.2, U2.43 (XTIN), Y1.3 (2)
unnamed: R27.1, U2.48 (EECS), U5.5 (CS)
unnamed: C3.2, U2.44 (XTOUT), Y1.1
unnamed: R30.1, U2.1 (EESK), U5.4 (CLK)
unnamed: R32.1, U2.2 (EEDATA), U5.3 (DI)
unnamed: C1.2, U2.6 (3V3OUT)
unnamed: R17.2, U2.40 (BDBUS0)
unnamed: R6.2, U2.39 (BDBUS1)
unnamed: R20.2, U2.24 (ADBUS0)
unnamed: R19.2, U2.19 (ADBUS5)
unnamed: R18.2, U2.17 (ADBUS6)
unnamed: R22.1, U$4.5 (2A)
unnamed: R21.1, U$4.6 (2Y)
unnamed: C6.2, R25.2, U2.46 (AVCC)
unnamed: R31.1, R32.2, U5.1 (DO)
unnamed: R33.2, U2.10 (SI/WUA)
unnamed: R34.2, U2.26 (SI/WUB)
RST: R21.2; also elsewhere on the board
SOP2: R23.2; also elsewhere on the board
TCK: R23.1, U$4.3 (1Y)
USB_D+: R28.2; also elsewhere on the board
USB_D-: R29.2; also elsewhere on the board
USB_DM: R29.1, U2.8 (USBDM)
USB_DP: R26.2, R28.1, U2.7 (USBDP)
VCC: R24.1, R27.2, R30.2, R31.2, R33.1, U2.14 (VCCIOA), U2.31 (VCCIOB), U5.6 (VCC), U$4.14 (VCC); also elsewhere on the board

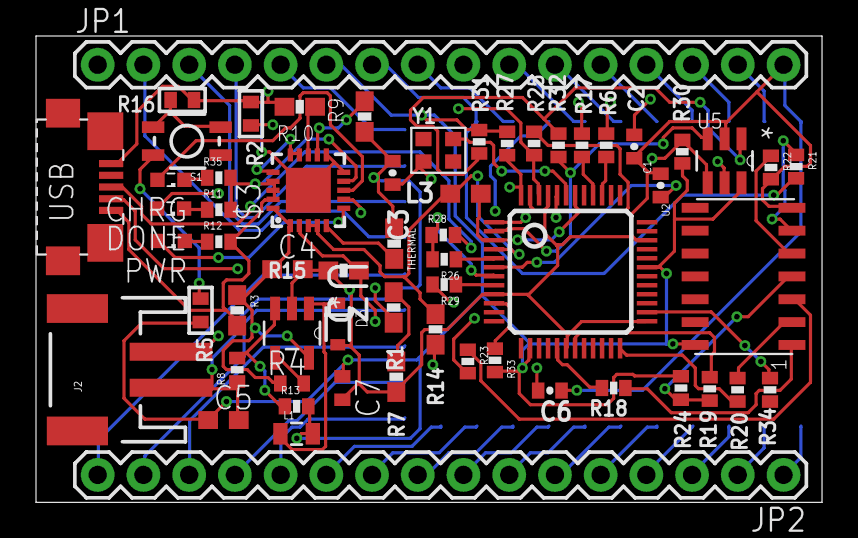
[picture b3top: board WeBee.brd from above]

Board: 4 copper layers, 43.7 x 25.9 mm, 61 parts (1 on the bottom side), 76 nets.

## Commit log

2014-12-20 Footprint
2014-12-20 Symbol
2014-12-23 Fixed a pad
2014-12-28 smd and Antenna
    smd pins updated
2015-01-25 Update lib
2015-01-25 Fixed some pads
2015-01-28 change title
2015-01-28 Add Bom file
2015-01-28 Completed Bom
2015-02-11 New library and Breakout
2015-02-16 switch charger
2015-02-16 add zip
2015-02-17 Added FTDI reroute
2015-02-17 via added
2015-02-17 Fix some un-routed ground
2015-02-17 more ground fixed
2015-02-17 Finish un-routed grounds
2015-02-17 Add gerber
2015-02-18 New Image added
2015-02-18 Accelerometer Sensor Added
2015-02-18 Accelerometer BMA220 Library Added
2015-02-18 Added a Ferrite
2015-02-19 Added EEPROM for FTDI chip
2015-02-20 Temp Sensor added
2015-02-20 added module IV-CC3200MOD
2015-02-20 Finished IV-CC3200MOD Eagle Library
2015-02-20 Eagle files for IV-CC3200MOD
2015-02-20 Starting WeeBee WiFi
2015-02-21 Labeled pins for WeeBee
2015-02-21 Added WeBee WiFi CC3200
2015-02-22 Finished WeBee
2015-02-23 Some cleanup
2015-02-23 Correct a mistake in lib
    The lib was reversed
2015-02-27 add image
2015-03-02 Micros USB connector library
2015-03-03 replace chip
2015-03-06 ftdi changes
2015-03-06 move the file
2015-03-06 moving folders
2015-03-06 Add Power Jumper
2015-03-07 added accelormeter
2015-03-08 Moved Micro USB and LiPo Connector to other side
2015-03-08 Fixed some grounds
2015-03-10 Revert "Add Power Jumper"
    This reverts commit 700f51e2ac70f058cb62d27b6654cd07e4fedc2f.
2015-03-10 Revert "Revert "Add Power Jumper""
    This reverts commit b415bd761c814d9cc5c4abbe20d7a3c3b9f7d0eb.

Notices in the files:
parts and their libraries:
SparkFun-Aesthetics: Licensing: CC v3.0 Share-Alike You are welcome to use this library for commercial purposes.
SparkFun-Connectors: Licensing: Creative Commons ShareAlike 4.0 International - https://creativecommons.org/licenses/by-sa/4.0
